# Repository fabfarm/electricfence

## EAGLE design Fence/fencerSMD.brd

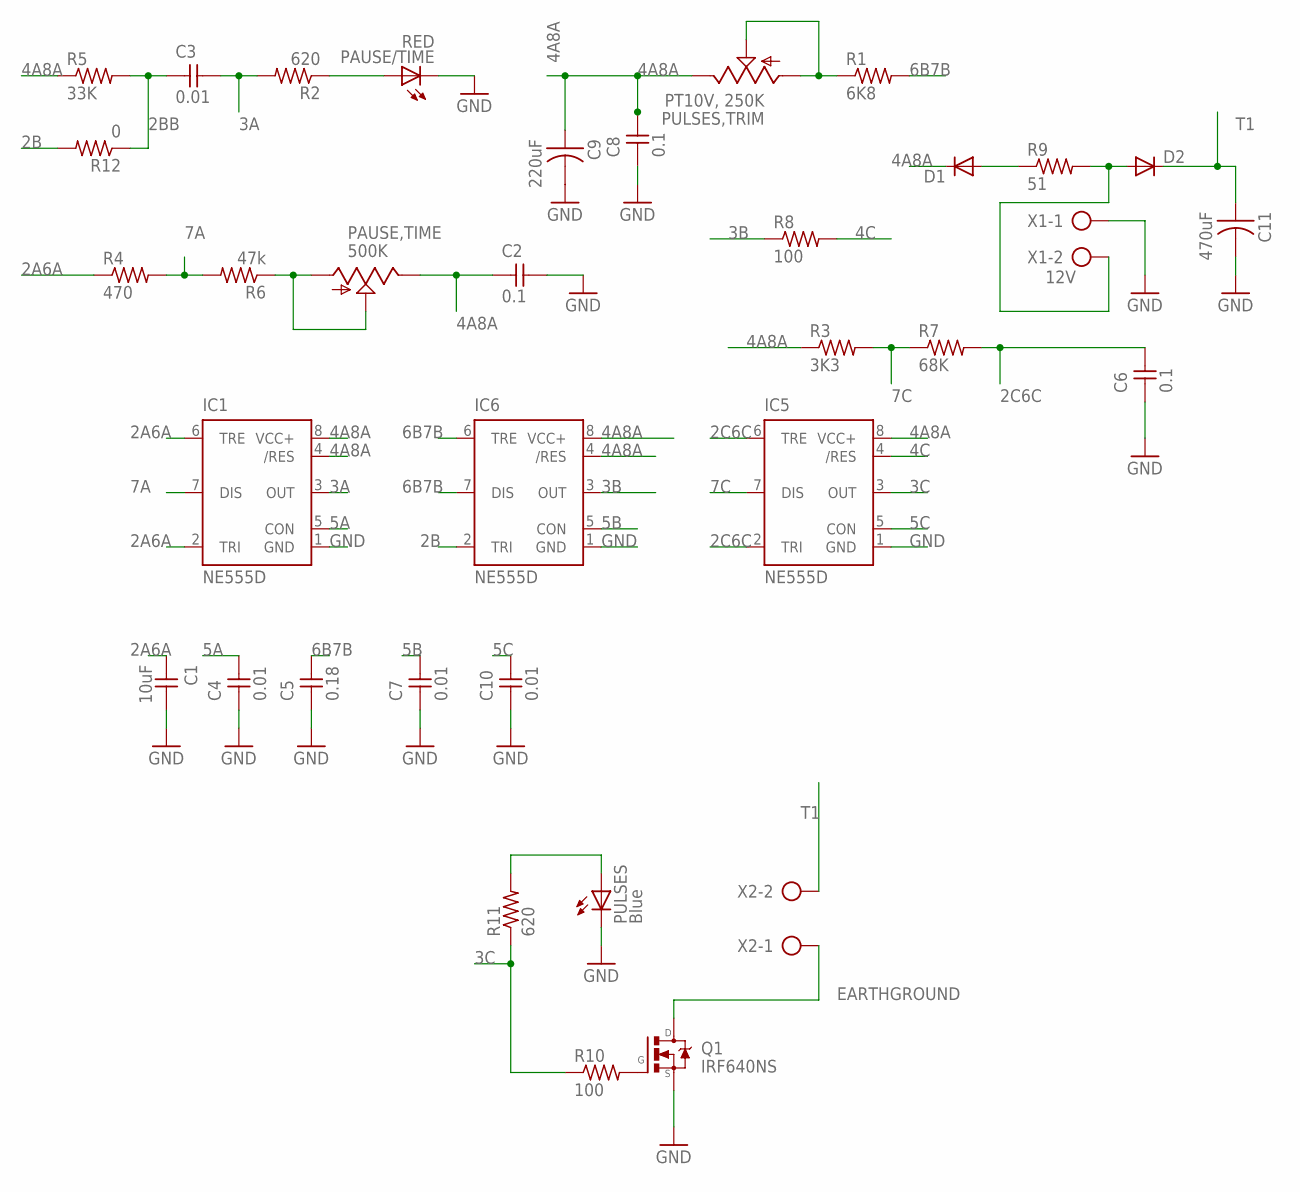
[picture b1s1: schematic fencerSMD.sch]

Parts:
C1: 10uF; 1206
C2, C6, C8: 0.1; 1206
C3, C4, C7, C10: 0.01; 1206
C5: 0.18; 1206
C9: 220uF; C1206
C11: 470uF; C1206
D1, D2: DIODESOD123; SOD123
IC1, IC5, IC6: NE555D; SO08
PAUSE,TIME: 500K; 6MM
PAUSE/TIME: RED; LED1206FAB
PULSES: Blue; LED1206FAB
PULSES,TRIM: PT10V, 250K; 6MM
Q1: IRF640NS; D2PAK
R1: 6K8; 1206
R2, R11: 620; 1206
R3: 3K3; 1206
R4: 470; 1206
R5: 33K; 1206
R6: 47k; 1206
R7: 68K; 1206
R8, R10: 100; 1206
R9: 51; 1206
R12: 0; 1206
X1: 12V; AK500/2-H
X2: AK500/2-H

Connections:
2A6A: C1.1, IC1.2 (TRI), IC1.6 (TRE), R4.1
2B: IC6.2 (TRI), R12.2
2BB: C3.1, R5.2, R12.1
2C6C: C6.2, IC5.2 (TRI), IC5.6 (TRE), R7.2
3A: C3.2, IC1.3 (OUT), R2.2
3B: IC6.3 (OUT), R8.1
3C: IC5.3 (OUT), R10.1, R11.1
4A8A: C2.1, C8.2, C9.1, D1.CATHODE (C), IC1.4 (/RES), IC1.8 (VCC+), IC5.8 (VCC+), IC6.4 (/RES), IC6.8 (VCC+), PAUSE,TIME.E, PULSES,TRIM.E, R3.1, R5.1
4C: IC5.4 (/RES), R8.2
5A: C4.2, IC1.5 (CON)
5B: C7.2, IC6.5 (CON)
5C: C10.2, IC5.5 (CON)
6B7B: C5.2, IC6.6 (TRE), IC6.7 (DIS), R1.2
7A: IC1.7 (DIS), R4.2, R6.2
7C: IC5.7 (DIS), R3.2, R7.1
ACC: D2.ANODE (A), R9.2, X1.2
EARTHGROUND: Q1.2 (D), X2.1
GND: C1.2, C2.2, C4.1, C5.1, C6.1, C7.1, C8.1, C9.2, C10.1, C11.2, IC1.1 (GND), IC5.1 (GND), IC6.1 (GND), PAUSE/TIME.2 (C), PULSES.2 (C), Q1.3 (S), X1.1
unnamed: PULSES,TRIM.A, PULSES,TRIM.S, R1.1
unnamed: PAUSE/TIME.1 (A), R2.1
unnamed: D1.ANODE (A), R9.1
unnamed: PAUSE,TIME.A, PAUSE,TIME.S, R6.1
unnamed: PULSES.1 (A), R11.2
unnamed: Q1.1 (G), R10.2
T1: C11.1, D2.CATHODE (C), X2.2

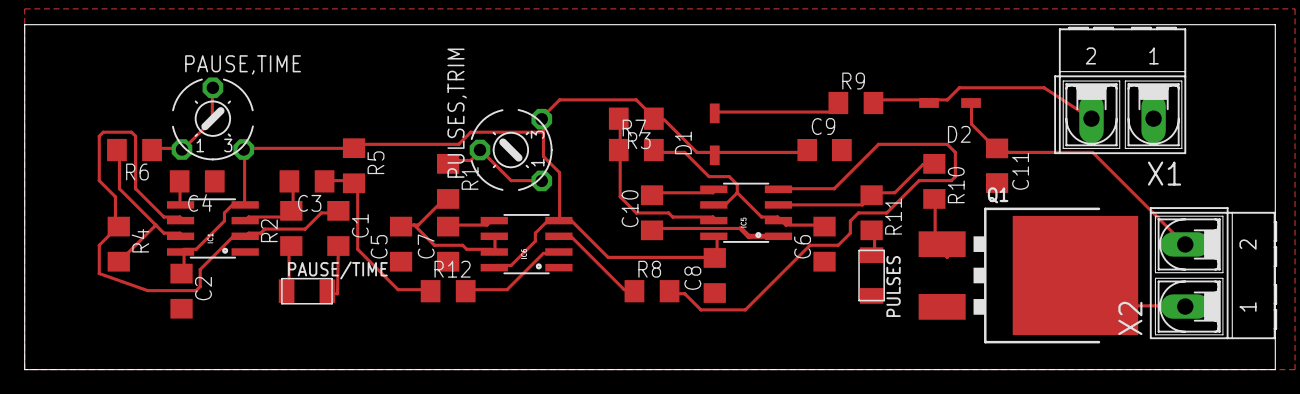
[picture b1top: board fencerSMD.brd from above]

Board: 2 copper layers, 101.3 x 27.9 mm, 35 parts (0 on the bottom side), 25 nets.

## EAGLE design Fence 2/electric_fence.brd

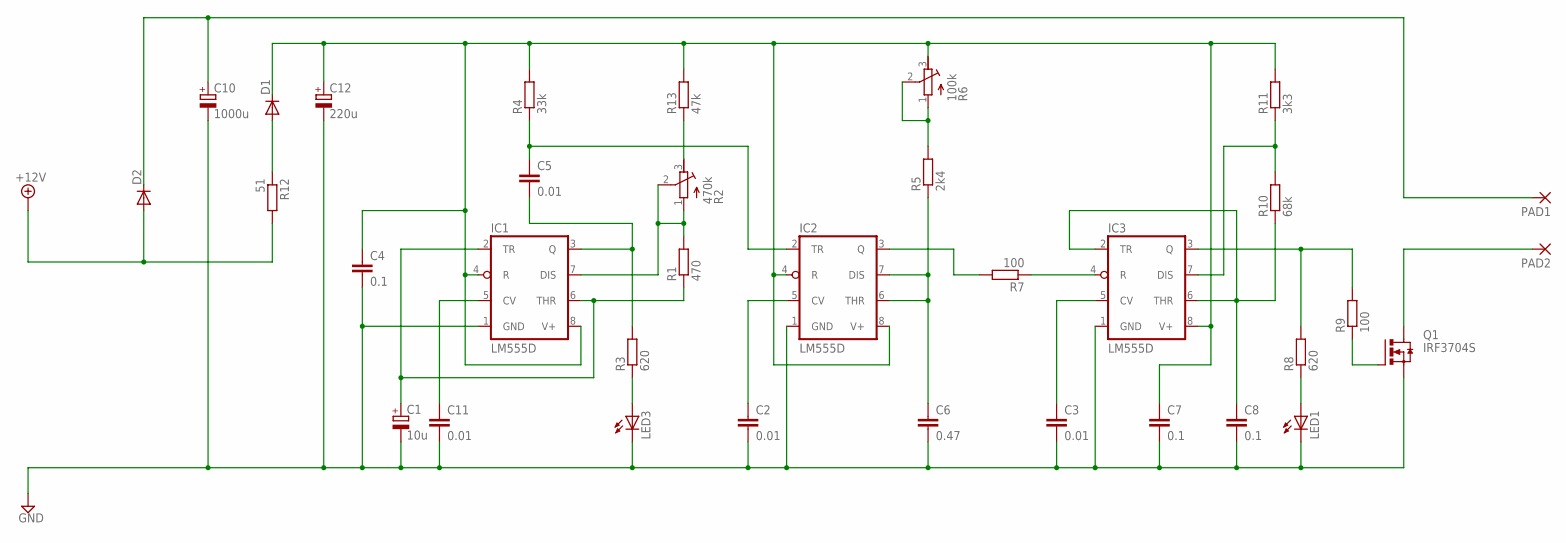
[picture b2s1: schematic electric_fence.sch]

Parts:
C1: 10u; E2-4
C2, C3, C5, C11: 0.01; C0402
C4, C7, C8: 0.1; C0402
C6: 0.47; C0402
C10: 1000u; E2-4
C12: 220u; E2-4
D1, D2: DIODE-DO-214AC; DO-214AC
IC1, IC2, IC3: LM555D; SO08
LED1, LED3: LEDCHIP-LED0805; CHIP-LED0805
PAD1, PAD2: SMD5; SMD2,54-5,08
Q1: IRF3704S; D2PACK
R1: 470; R0805
R2: 470k; RTRIM4G/J
R3, R8: 620; R0805
R4: 33k; R0805
R5: 2k4; R0805
R6: 100k; RTRIM4G/J
R7, R9: 100; R0805
R10: 68k; R0805
R11: 3k3; R0805
R12: 51; R0805
R13: 47k; R0805

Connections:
+12V: D2.A, R12.2
GND: C1.-, C2.2, C3.2, C4.2, C6.2, C7.2, C8.2, C10.-, C11.2, C12.-, IC1.1 (GND), IC2.1 (GND), IC3.1 (GND), LED1.C, LED3.C, Q1.3 (S)
unnamed: C2.1, IC2.5 (CV)
unnamed: C3.1, IC3.5 (CV)
unnamed: R5.2, R6.1 (A), R6.2 (S)
unnamed: C1.+, IC1.2 (TR), IC1.6 (THR), R1.1
unnamed: IC1.7 (DIS), R1.2, R2.1 (A), R2.2 (S)
unnamed: C5.2, IC1.3 (Q), R3.2
unnamed: LED3.A, R3.1
unnamed: C5.1, IC2.2 (TR), R4.1
unnamed: C6.1, IC2.6 (THR), IC2.7 (DIS), R5.1
unnamed: IC2.3 (Q), R7.2
unnamed: IC3.4 (R), R7.1
unnamed: C8.1, IC3.2 (TR), IC3.6 (THR), R10.1
unnamed: C11.1, IC1.5 (CV)
unnamed: C4.1, C7.1, C12.+, D1.C, IC1.4 (R), IC1.8 (V+), IC2.4 (R), IC2.8 (V+), IC3.8 (V+), R4.2, R6.3 (E), R11.2, R13.2
unnamed: IC3.3 (Q), R8.2, R9.2
unnamed: LED1.A, R8.1
unnamed: C10.+, D2.C, PAD1.1
unnamed: Q1.1 (G), R9.1
unnamed: D1.A, R12.1
unnamed: PAD2.1, Q1.2 (D)
unnamed: IC3.7 (DIS), R10.2, R11.1
unnamed: R2.3 (E), R13.1

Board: 2 copper layers, 34 parts (0 on the bottom side), 24 nets, no tracks yet.

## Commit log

2017-04-30 Original circuit added.
2017-05-14 Outra versão.
2017-05-14 Temp files deleted.
2017-05-15 Updating stuff that was not before
2017-06-20 Delete

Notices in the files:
parts and their libraries:
SparkFun-AnalogIC: Licensing: CC v3.0 Share-Alike You are welcome to use this library for commercial purposes.
